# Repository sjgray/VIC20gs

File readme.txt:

VIC-20 GS
=========

This is an early attempt to learn kicad and also to learn how to create an IC library.
This design is for a VIC-20 "Game System" as imagined by me. It does not
include cassette interface or power components onboard. I have added extra features.

This design has not been verified, breadboarded or routed so use at own risk. It is
released as-is and may contain errors.

Project webpage is loacated at:

http://www.cbmsteve.ca
http://www.cbmsteve.ca/vic20r/index.html

Steve

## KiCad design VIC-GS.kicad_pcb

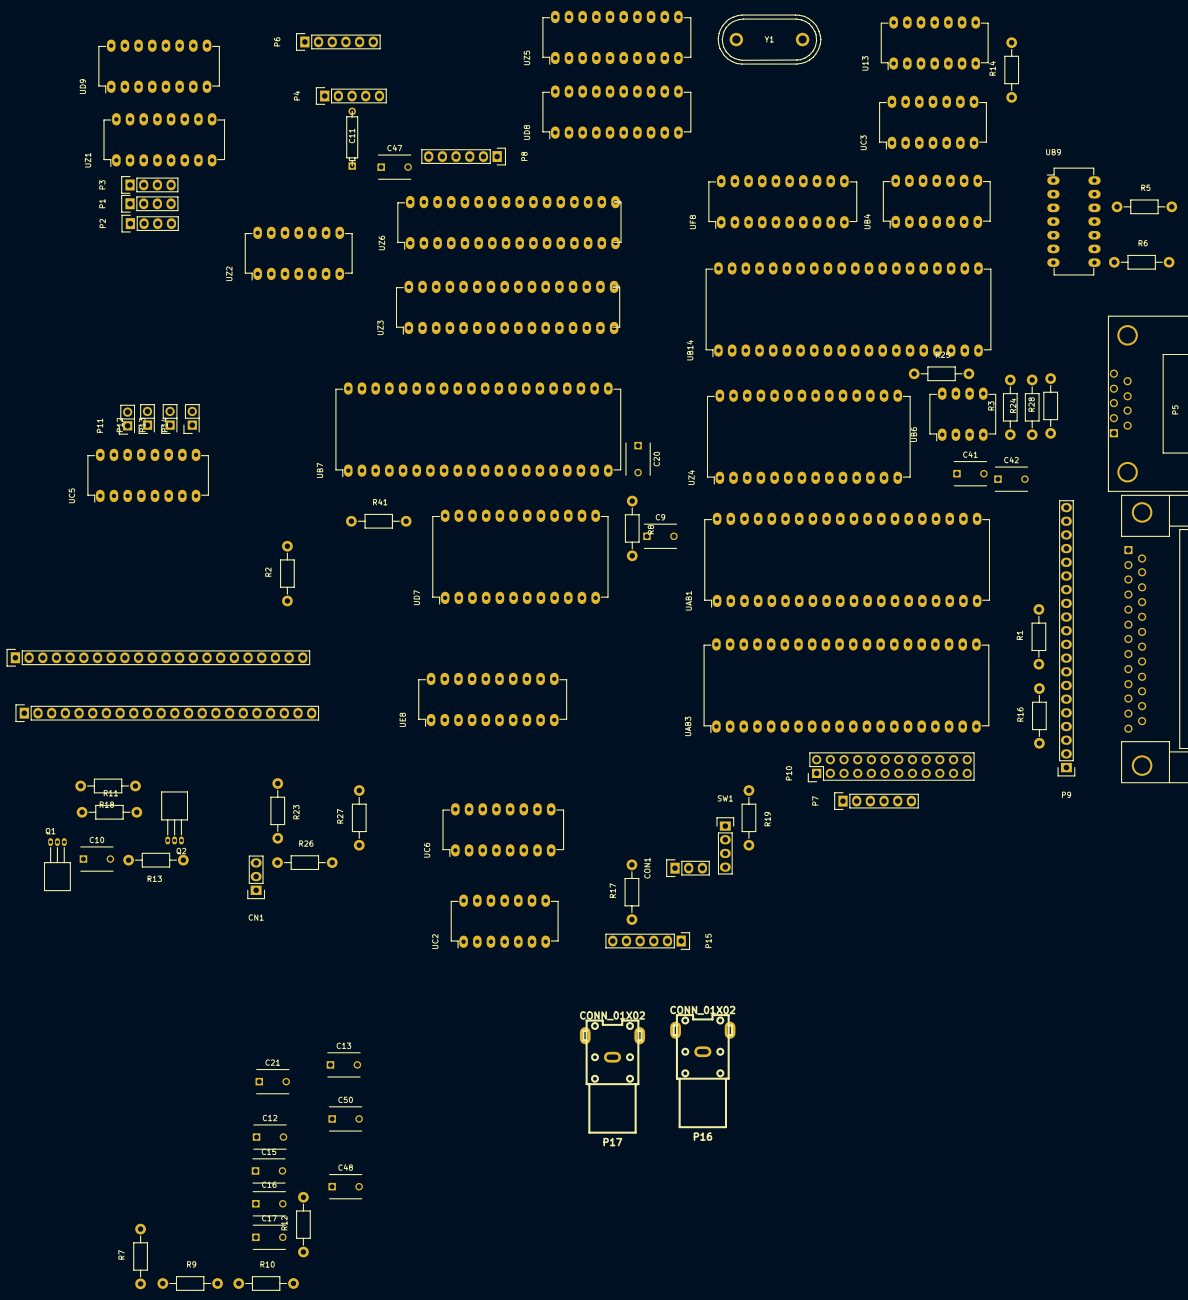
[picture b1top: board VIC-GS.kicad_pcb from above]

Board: 2 copper layers, 88 parts (0 on the bottom side), 167 nets, no tracks yet.

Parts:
C9, C10, C12, C13, C15, C16, C17, C20, C21, C41, C42, C47, C50: C; C_Disc_D6_P5
C11: CP; CP4
C48: CTRIM; C_Disc_D6_P5
CN1: CONN_01X03; Pin_Header_Straight_1x03
CON1: BARREL_JACK; Pin_Header_Straight_1x03
J1: DB25; DB25FC
P1, P2, P3: CONN_01X04; Pin_Header_Straight_1x04
P4: CONN_01X05; Pin_Header_Straight_1x05
P5: DB9; DB9MC
P6, P7, P8, P15: CONN_01X06; Pin_Header_Straight_1x06
P6B1, P6T1: CONN_01X22; Pin_Header_Straight_1x22
P9: CONN_01X20; Pin_Header_Straight_1x20
P10: CONN_02X12; Pin_Header_Straight_2x12
P11, P12, P13, P14: CONN_02X01; Pin_Header_Straight_2x01
P16: CONN_01X02; rca_yellow
P17: CONN_01X02; rca_white
Q1, Q2: 2SC1815; TO-92_Horizontal1_Inline_Narrow_Oval
R1, R2, R3: 2.2K; Resistor_Horizontal_RM10mm
R5, R6, R23: 330; Resistor_Horizontal_RM10mm
R7: 560; Resistor_Horizontal_RM10mm
R8, R10, R17, R18, R19, R26: 1K; Resistor_Horizontal_RM10mm
R9: 510; Resistor_Horizontal_RM10mm
R11: 1.8K; Resistor_Horizontal_RM10mm
R12: 2.7K; Resistor_Horizontal_RM10mm
R13: 270; Resistor_Horizontal_RM10mm
R14: 180; Resistor_Horizontal_RM10mm
R16: 10K; Resistor_Horizontal_RM10mm
R24: 220M; Resistor_Horizontal_RM10mm
R25: 150K; Resistor_Horizontal_RM10mm
R27: 470; Resistor_Horizontal_RM10mm
R28: 360; Resistor_Horizontal_RM10mm
R41: 240; Resistor_Horizontal_RM10mm
SW1: Switch_DPST; Pin_Header_Straight_1x04
U13: 74LS08; DIP-14_W7.62mm_LongPads
UAB1, UAB3: 6522; DIP-40_W15.24mm_LongPads
UB4: 74LS06; DIP-14_W7.62mm_LongPads
UB6: LM555N; DIP-8_W7.62mm_LongPads
UB7: 6560; DIP-40_W15.24mm_LongPads
UB9: 7402; DIP-14_W7.62mm_LongPads
UB14: 6502; DIP-40_W15.24mm_LongPads
UC2: 74LS04; DIP-14_W7.62mm_LongPads
UC3: 74LS02; DIP-14_W7.62mm_LongPads
UC5, UC6: 74LS138; DIP-16_W7.62mm_LongPads
UD7: 2332; DIP-24_W15.24mm_LongPads
UD8: 74LS245; DIP-20_W7.62mm_LongPads
UD9: 74LS133; DIP-16_W7.62mm_LongPads
UE8: 74LS245; DIP-20_W7.62mm_LongPads
UF8: 74LS245; DIP-20_W7.62mm_LongPads
UZ1: 74LS133; DIP-16_W7.62mm_LongPads
UZ2: 7400; DIP-14_W7.62mm_LongPads
UZ3, UZ6: UM61512A; DIP-32_W7.62mm_LongPads
UZ4: 27512; DIP-28_W15.24mm_LongPads
UZ5: 74LS245; DIP-20_W7.62mm_LongPads
Y1: Crystal; Crystal_HC48-U_Vertical

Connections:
5V: C12.1, C15.1, C16.1, C47.1, P1.1, P1.2, P1.3, P1.4, P4.1, P5.7, P6T1.21, P9.4, P10.3, Q1.2, Q2.2, R1.1, R2.1, R3.1, R7.1, R9.1, R11.1, R14.2, R16.2, R17.2, R18.2, R19.2, R23.2, R24.1, R25.1, R26.1, R28.1, SW1.3, UB6.4, UD9.1, UZ1.6, UZ1.7, UZ1.10, UZ1.11, UZ1.12, UZ1.13, UZ1.14, UZ1.15, UZ3.30, UZ6.30
A0: P6B1.2, UAB1.38, UAB3.38, UB14.9, UD8.2, UZ4.10
A1: P6B1.3, UAB1.37, UAB3.37, UB14.10, UD8.3, UZ4.9
A2: P6B1.4, UAB1.36, UAB3.36, UB14.11, UD8.4, UZ4.8
A3: P6B1.5, UAB1.35, UAB3.35, UB14.12, UD8.5, UZ4.7
A4: P6B1.6, UAB3.24, UB14.13, UD8.6, UZ4.6
A5: P6B1.7, UAB1.24, UB14.14, UD8.7, UZ4.5
A6: P6B1.8, UB14.15, UD8.8, UZ4.4
A7: P6B1.9, UB14.16, UD8.9, UZ4.3
A8: P6B1.10, UB14.17, UE8.18, UZ4.25
A9: P6B1.11, UB14.18, UE8.17, UZ4.24
A10: P6B1.12, UB14.19, UC6.1, UE8.14, UZ4.21
A11: P6B1.13, UB14.20, UC6.2, UE8.13, UZ4.23
A12: P6B1.14, UB14.22, UC6.3, UE8.16, UZ4.2
A13: P6B1.15, UB14.23, UC5.1, UC6.4, UZ4.26
A14: UB14.24, UC5.2, UC6.5, UZ3.3
A15: UB14.25, UC5.3, UC6.6, UZ3.31
AUDIO_IN: C10.1, P6B1.21, Q1.3, R8.2
AUDIO_OUT: C11.2, P4.3, P17.1
BD0: UAB1.33, UAB3.33, UB7.16, UD7.9, UF8.2, UZ3.13, UZ5.2
BD1: UAB1.32, UAB3.32, UB7.15, UD7.10, UF8.3, UZ3.14, UZ5.3
BD2: UAB1.31, UAB3.31, UB7.14, UD7.11, UF8.4, UZ3.15, UZ5.4
BD3: UAB1.30, UAB3.30, UB7.13, UD7.13, UF8.5, UZ3.17, UZ5.5
BD4: UAB1.29, UAB3.29, UB7.12, UD7.14, UF8.6, UZ3.16, UZ5.6
BD5: UAB1.28, UAB3.28, UB7.11, UD7.15, UF8.7, UZ3.19, UZ5.7
BD6: UAB1.27, UAB3.27, UB7.10, UD7.16, UF8.8, UZ3.20, UZ5.8
BD7: UAB1.26, UAB3.26, UB7.9, UD7.17, UF8.9, UZ3.21, UZ5.9
BLK0: UC5.15, UZ1.1
BLK1: P2.1, P11.1, UC5.14, UD9.14
BLK2: P2.2, P12.1, UC5.13, UD9.13
BLK3: P2.3, P13.1, UC5.12, UD9.12
BLK4: UC5.11, UE8.15
BLK5: P2.4, P14.1, UC5.10, UD9.10
BLK6: UC5.9, UD9.15, UZ2.1
BLK7: UC5.7, UD9.7, UZ2.2
CHROMA: C13.2, UB7.2
COL0: P9.12, UAB1.10
COL1: P9.11, UAB1.11
COL2: P9.10, UAB1.12
COL3: P9.9, UAB1.13
COL4: P9.8, UAB1.14
COL5: P9.7, UAB1.15
COL6: P9.6, UAB1.16
COL7: P9.5, UAB1.17
COLOR: UC2.10, UE8.12
CPU_02: UB14.39, UC3.6
CS_RAM: UZ1.9, UZ3.22, UZ3.24, UZ6.22, UZ6.24
CS_ROM: UZ2.3, UZ4.20, UZ4.22
D0: P6T1.2, UB14.33, UF8.18, UZ4.11
D1: P6T1.3, UB14.32, UF8.17, UZ4.12
D2: P6T1.4, UB14.31, UF8.16, UZ4.13
D3: P6T1.5, UB14.30, UF8.15, UZ4.15
D4: P6T1.6, UB14.29, UF8.14, UZ4.16
D5: P6T1.7, UB14.28, UF8.13, UZ4.17
D6: P6T1.8, UB14.27, UF8.12, UZ4.18
D7: P6T1.9, UB14.26, UF8.11, UZ4.19
DATA_E: UD9.9, UF8.19
E: UB4.11, UB7.35, UC3.11, UD8.19, UE8.19
GND: C9.2, C10.2, C15.2, C16.2, C20.2, C21.2, C41.2, C42.2, CN1.2, P4.2, P5.8, P6.1, P6.2, P6.3, P6.4, P6.5, P6.6, P6B1.1, P6B1.22, P6T1.1, P6T1.22, P9.1, P10.1, P10.2, P10.21, P10.23, P10.24, P15.2, P16.2, P17.2, R12.2, R13.2, R27.2, SW1.1, U13.7, UAB1.1, UAB3.1, UB4.7, UB6.1, UB7.20, UB9.7, UB14.21, UC2.7, UC3.7, UC5.4, UC5.5, UC5.8, UC6.8, UD7.12, UD8.10, UD9.8, UE8.1, UE8.10, UF8.10, UZ1.8, UZ2.7, UZ4.1, UZ4.14, UZ4.27, UZ5.10
I/O0: UAB1.23, UAB3.23, UC6.11
I/O2: P6B1.16, UD9.6
I/O3: P6B1.17, UD9.5
IRQ: P6T1.19, R1.2, UAB1.21, UB14.4
JOY0: P5.1, P10.7, UAB3.4
JOY1: P5.2, P10.9, UAB3.5
JOY2: P5.3, P10.11, UAB3.6
LPEN: P5.6, P10.13, UAB3.7, UB7.37
LUMA: R41.1, UB7.3
NMI: P6B1.19, R2.2, UAB3.21, UB14.6
unnamed: C11.1, Q1.1, R27.1
unnamed: C13.1, R9.2, R10.1, R41.2
unnamed: C17.1, Q2.3, R11.2, R12.1
unnamed: C17.2, R10.2
unnamed: C41.1, R24.2, UB6.2
unnamed: C42.1, R25.2, UB6.6, UB6.7
unnamed: C47.2, UD8.1
unnamed: C48.1, C50.1, Y1.2
unnamed: C48.2, C50.2, R6.1, UB9.1, UB9.8, UB9.9
unnamed: CN1.1, CN1.3, R23.1
unnamed: CON1.1, SW1.4
unnamed: CON1.2, SW1.2
unnamed: P3.1, UZ1.2
unnamed: P3.2, UZ1.3
unnamed: P3.3, UZ1.4
unnamed: P3.4, UZ1.5
unnamed: P8.1, UZ6.23
unnamed: P8.2, UZ6.25
unnamed: P8.3, UZ6.4
unnamed: P8.4, UZ6.28
unnamed: P8.5, UZ6.3
unnamed: P8.6, UZ6.31
unnamed: P6T1.10, P11.2
unnamed: P6T1.11, P12.2
unnamed: P6T1.12, P13.2
unnamed: P6T1.13, P14.2
unnamed: R5.1, R6.2, UB9.2, UB9.3, UB9.4, UB9.11, UB9.12
unnamed: R5.2, UB9.5, UB9.6, Y1.1
unnamed: UB4.1, UB6.3
unnamed: UC2.1, UC3.1
unnamed: UC2.2, UC3.12
unnamed: UC2.11, UC6.10
unnamed: UC2.13, UC3.13
PB0: P7.1, P10.6, UAB3.10
PB1: P7.2, P10.8, UAB3.11
PB2: P7.3, P10.10, UAB3.12
PB3: P7.4, P10.12, UAB3.13
PB4: P7.5, P10.14, UAB3.14
PB5: P7.6, P10.16, UAB3.15
PB6: P10.18, UAB3.16
PB7: P10.20, UAB3.17
POTX: C20.1, P5.9, UB7.17
POTY: C21.1, P5.5, UB7.18
R/~W: P6T1.17, UAB1.22, UAB3.22, UB14.34, UC3.2, UF8.1
RAM1: P6T1.14, UD9.11
RAM2: P6T1.15, UD9.3
RAM3: P6T1.16, UD9.2
RDY: R3.2, UB14.2, UB14.38
RESET: P6B1.20, P10.5, P15.6, R26.2, UAB1.34, UAB3.34, UB4.2, UB14.40
RESTORE: P9.3, R16.1, UAB1.40
ROW0: P9.20, UAB1.2
ROW1: P9.19, UAB1.3
ROW2: P9.18, UAB1.4
ROW3: P9.17, UAB1.5
ROW4: P9.16, UAB1.6
ROW5: P9.15, UAB1.7
ROW6: P9.14, UAB1.8
ROW7: P9.13, UAB1.9
S00: R14.1, UB4.10, UB14.37, UC3.5
S01: UB14.3, UC2.9, UC3.3, UC3.4
S02: P6B1.18, UAB1.25, UAB3.25, UC2.8, UC5.6, UD9.4, UZ5.1
SER_ATN_IN: P10.17, P15.3, R18.1, UB4.6
SER_ATN_OUT: UAB3.9, UB4.5
SER_CLK_IN: P15.4, R17.1, UAB3.2, UB4.12
SER_CLK_OUT: UAB1.39, UB4.13
SER_DATA_IN: P15.5, R19.1, UAB3.3, UB4.4
SER_DATA_OUT: UAB1.19, UB4.3
SER_SRQ: P15.1, UAB1.18
VA0: UB7.21, UD7.8, UD8.18, UZ3.12, UZ6.12
VA1: UB7.22, UD7.7, UD8.17, UZ3.11, UZ6.11
VA2: UB7.23, UD7.6, UD8.16, UZ3.10, UZ6.10
VA3: UB7.24, UD7.5, UD8.15, UZ3.9, UZ6.9
VA4: UB7.25, UD7.4, UD8.14, UZ3.8, UZ6.8
VA5: UB7.26, UD7.3, UD8.13, UZ3.7, UZ6.7
VA6: UB7.27, UD7.2, UD8.12, UZ3.6, UZ6.6
VA7: UB7.28, UD7.1, UD8.11, UZ3.5, UZ6.5
VA8: UB7.29, UD7.23, UE8.2, UZ3.27, UZ6.27
VA9: UB7.30, UD7.22, UE8.3, UZ3.26, UZ6.26
VA10: UB7.31, UD7.19, UE8.6, UZ3.23
VA11: UB7.32, UD7.18, UE8.7, UZ3.25
VA12: UB7.33, UD7.21, UE8.4, UZ3.4
VA13: UB7.34, UD7.20, UE8.5, UZ3.28
VCC: U13.14, UAB1.20, UAB3.20, UB4.14, UB6.8, UB7.40, UB9.14, UB14.8, UC2.14, UC3.14, UC5.16, UC6.16, UD7.24, UD8.20, UD9.16, UE8.20, UF8.20, UZ1.16, UZ2.14, UZ4.28, UZ5.20
VD8: UB7.8, UZ5.18, UZ6.13
VD9: UB7.7, UZ5.17, UZ6.14
VD10: UB7.6, UZ5.16, UZ6.15
VD11: UB7.5, UZ5.15, UZ6.17
VD12: UZ5.14, UZ6.16
VD13: UZ5.13, UZ6.19
VD14: UZ5.12, UZ6.20
VD15: UZ5.11, UZ6.21
VIA2_CB1: P10.4, UAB3.18
VIA2_CB2: P10.22, UAB3.19
VICAUDIO: C9.1, R8.1, UB7.19
VIC_01: R7.2, UB7.39, UB9.13
VIC_02: R28.2, UB7.38, UB9.10
VIDEO_OUT: P4.4, P4.5, P16.1, Q2.1, R13.1
VR/~W: P6T1.18, UB7.4, UC2.12, UZ3.29, UZ6.29

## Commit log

2020-12-19 :tada: Added .gitattributes & .gitignore files
2020-12-19 VIC-20 Game System
    Initial Release. This has not been tested or verified and is released
    as-is. Use at own risk.
2025-01-15 Update webpage
    http://www.cbmsteve.ca/
